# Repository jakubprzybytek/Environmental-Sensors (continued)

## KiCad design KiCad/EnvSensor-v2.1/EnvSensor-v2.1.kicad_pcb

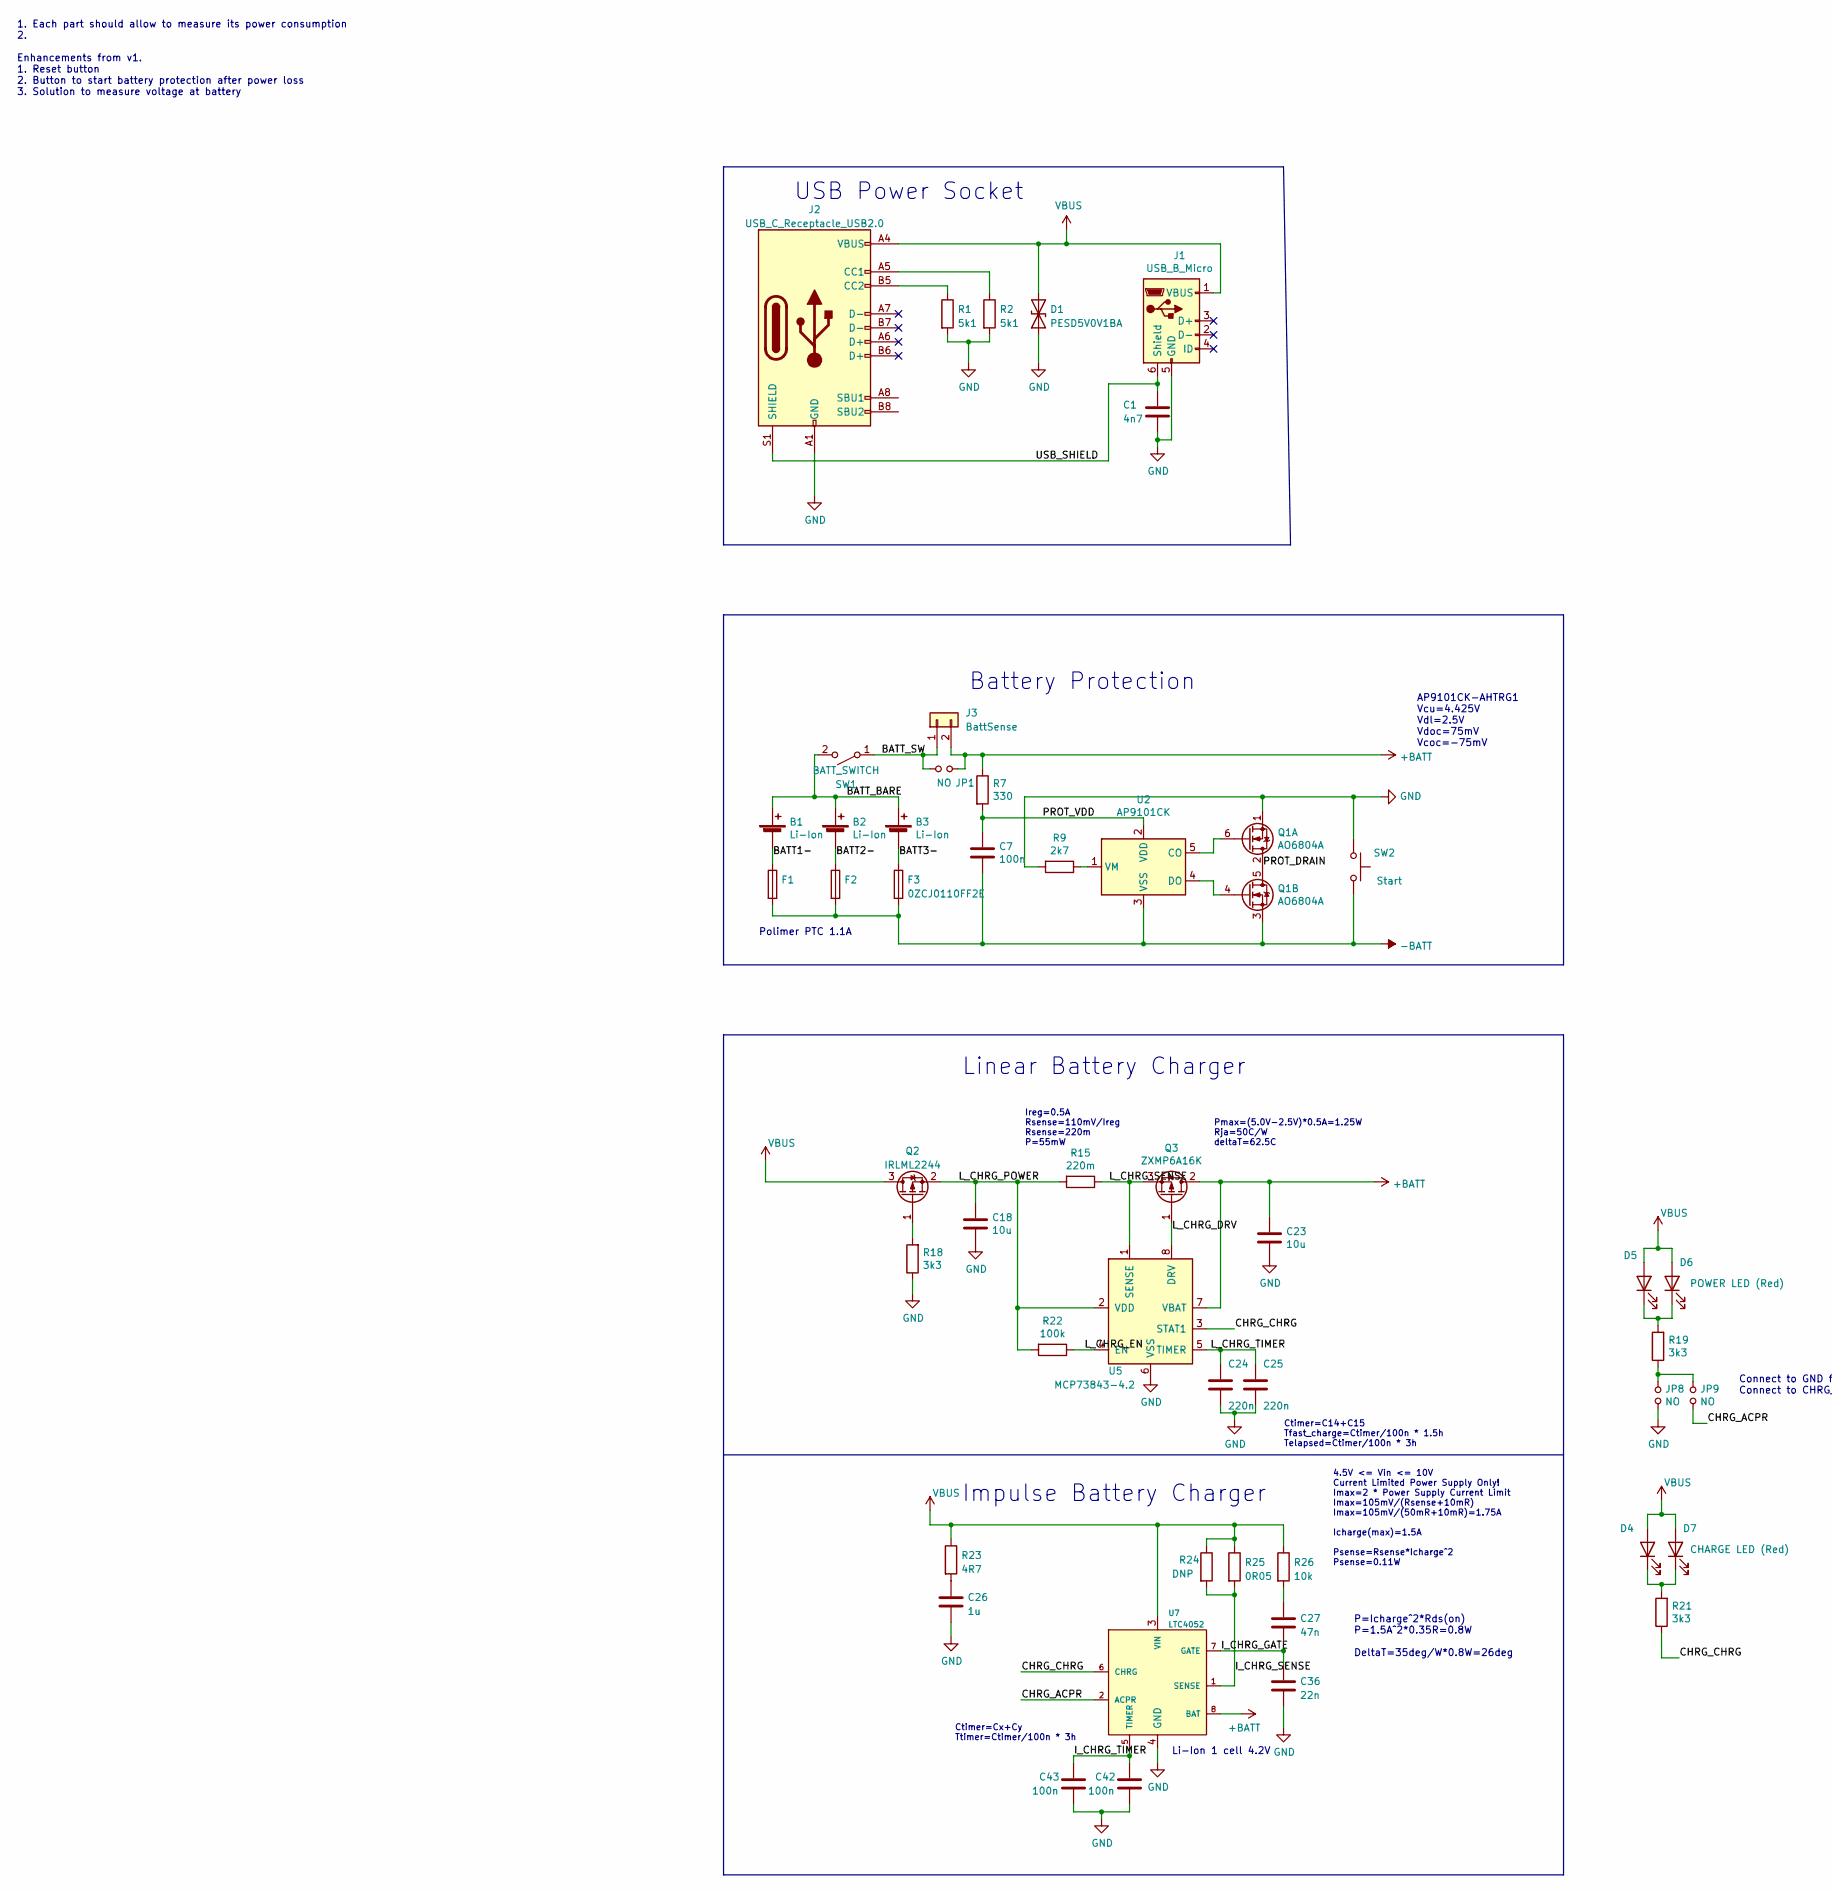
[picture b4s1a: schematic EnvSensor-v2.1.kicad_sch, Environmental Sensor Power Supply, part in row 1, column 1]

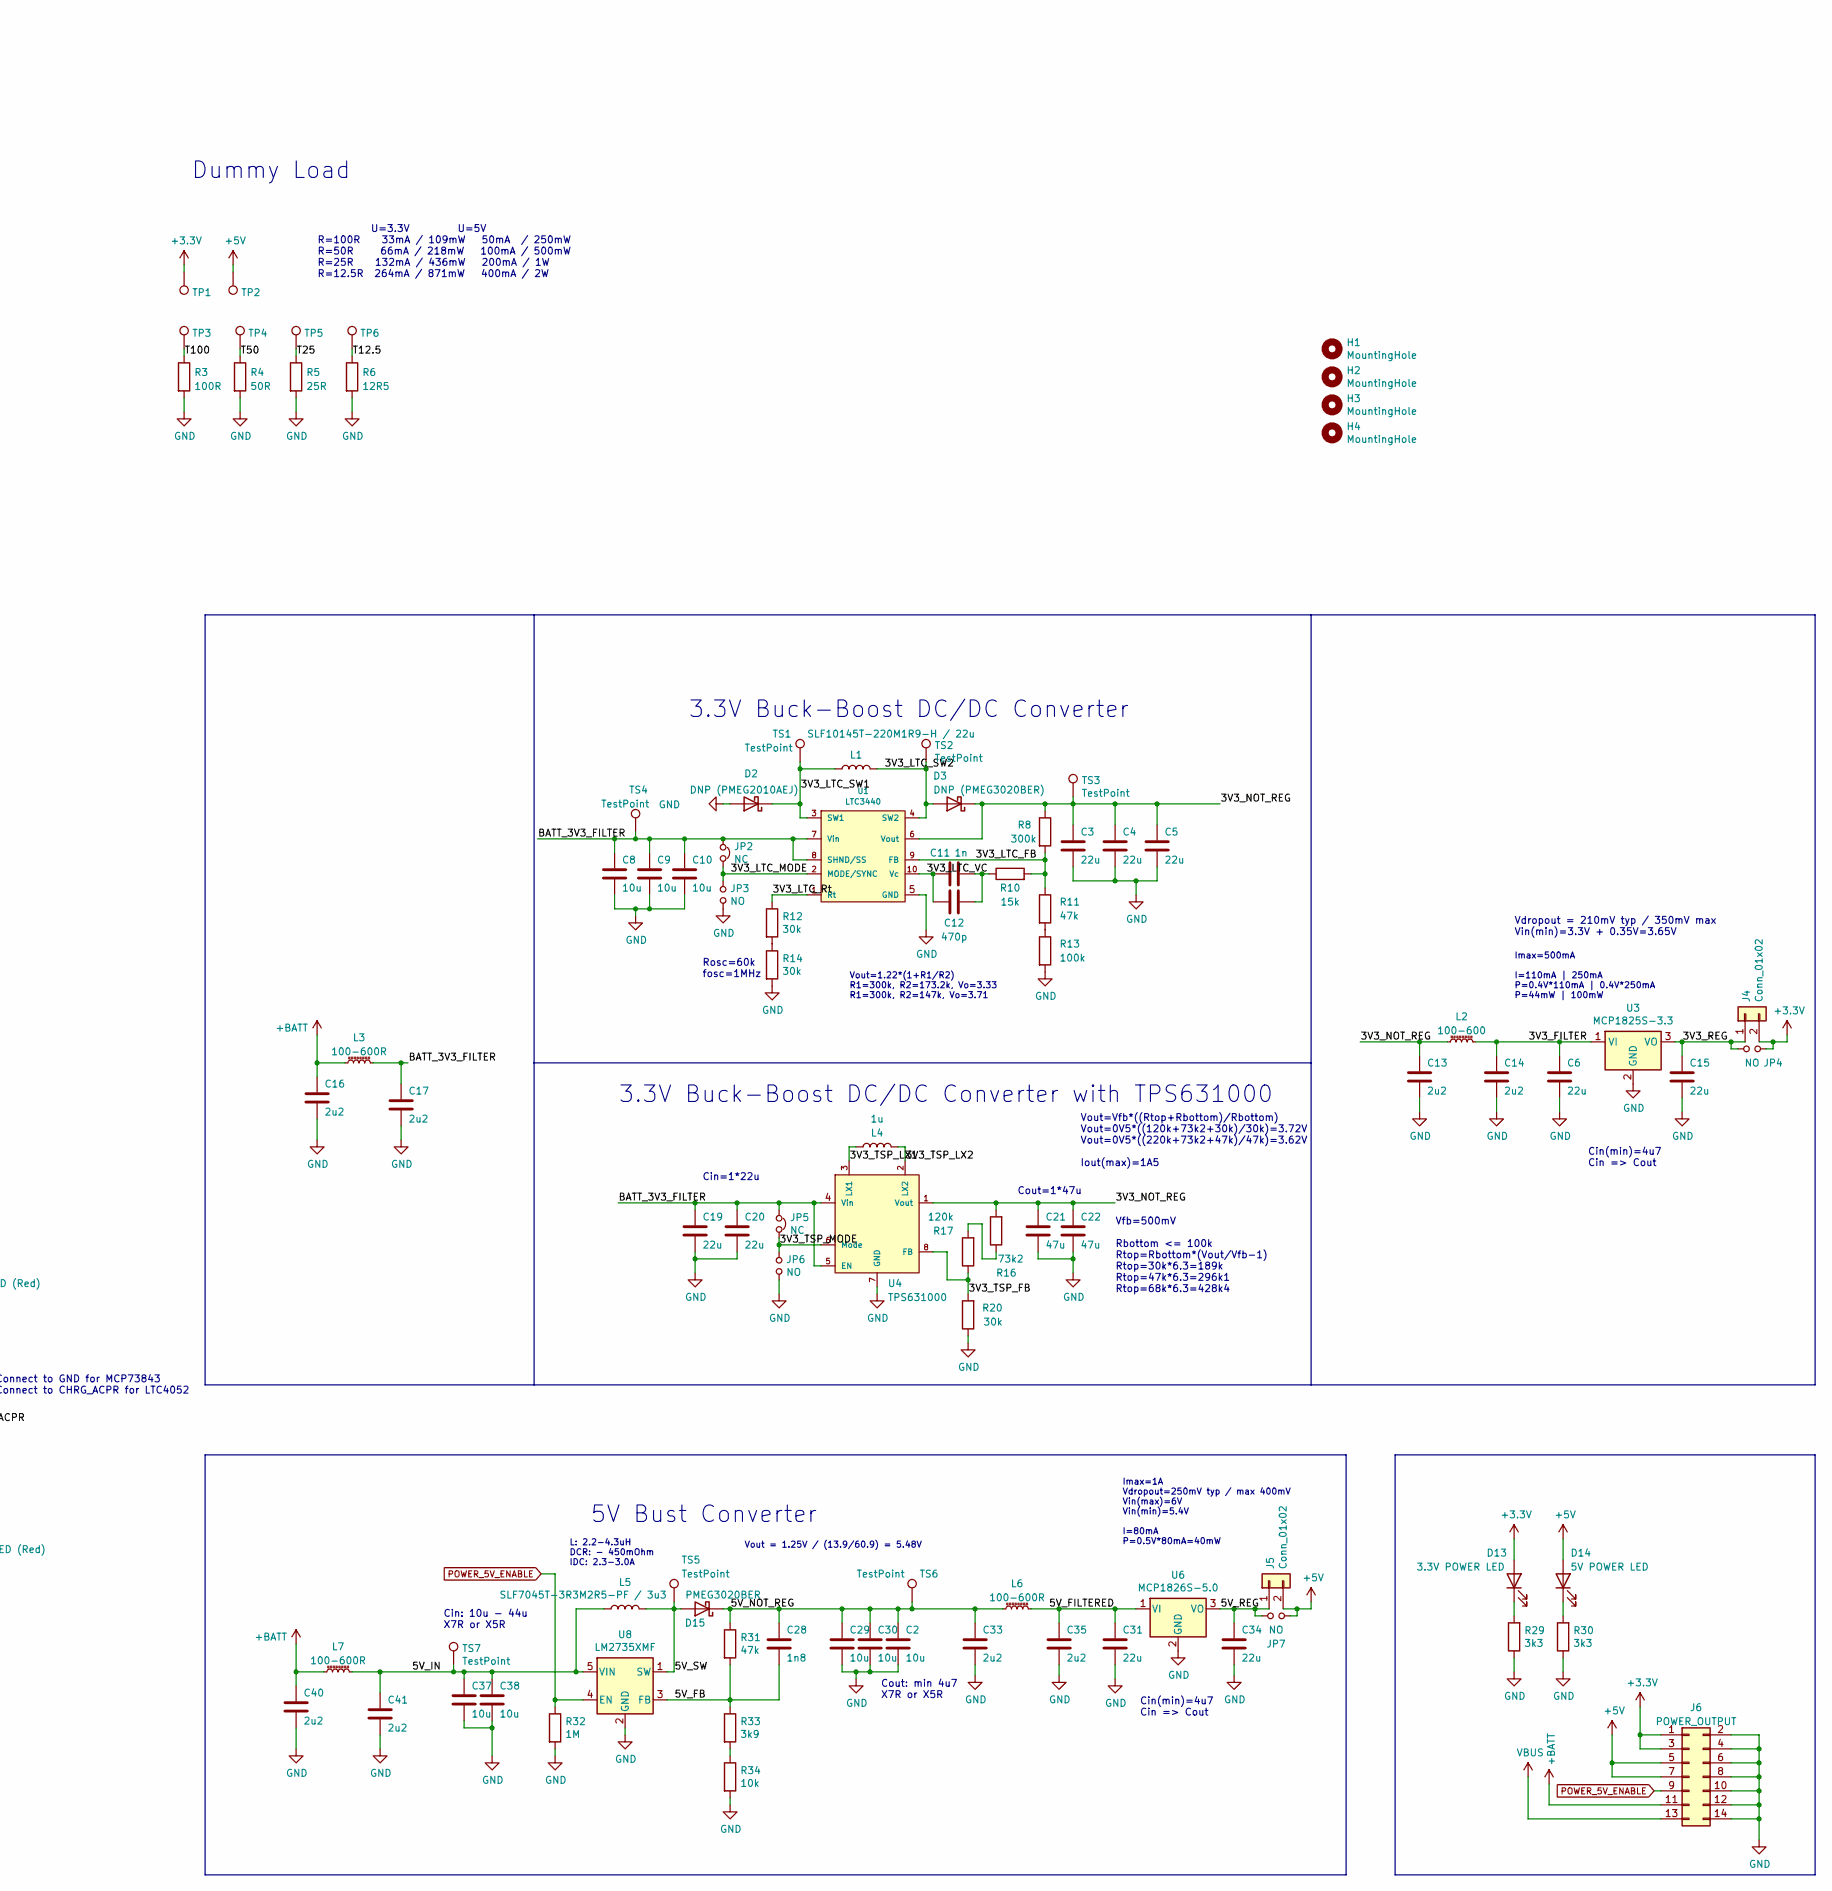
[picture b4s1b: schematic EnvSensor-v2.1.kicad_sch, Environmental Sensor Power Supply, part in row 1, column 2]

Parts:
B1, B2, B3: Li-Ion; BatteryHolder_Keystone_1042_1x18650
C1: 4n7; C_0805_2012Metric
C2, C29, C30: 10u; C_1206_3216Metric
C3, C4, C5, C6, C15, C19, C20, C31, C34: 22u; C_1206_3216Metric
C7, C42, C43: 100n; C_0603_1608Metric
C8, C9, C10, C18, C23, C37, C38: 10u; C_0805_2012Metric
C11: 1n; C_0805_2012Metric
C12: 470p; C_0805_2012Metric
C13, C14, C16, C17, C33, C35, C40, C41: 2u2; C_0805_2012Metric
C21, C22: 47u; C_1206_3216Metric
C24, C25: 220n; C_0805_2012Metric
C26: 1u; C_0805_2012Metric
C27: 47n; C_0805_2012Metric
C28: 1n8; C_0805_2012Metric
C36: 22n; C_0805_2012Metric
D1: PESD5V0V1BA; D_SOD-323
D2: DNP (PMEG2010AEJ); D_SOD-323_HandSoldering
D3: DNP (PMEG3020BER); D_SOD-123
D4, D5: POWER LED; LED_0805_2012Metric
D6: POWER LED (Red); LED_D3.0mm_Horizontal_O3.81mm_Z6.0mm
D7: CHARGE LED (Red); LED_D3.0mm_Horizontal_O3.81mm_Z6.0mm
D13: 3.3V POWER LED; LED_0805_2012Metric
D14: 5V POWER LED; LED_0805_2012Metric
D15: PMEG3020BER; D_SOD-123
F1, F2, F3: 0ZCJ0110FF2E; Fuse_1206_3216Metric
H1, H2, H3, H4: MountingHole; MountingHole_3.2mm_M3
J1: USB_B_Micro; USB_Micro-B_Molex_47346-0001
J2: USB_C_Receptacle_USB2.0; USB_C_Receptacle_HRO_TYPE-C-31-M-12
J3: BattSense; PinHeader_1x02_P2.54mm_Vertical
J4, J5: Conn_01x02; PinHeader_1x02_P2.54mm_Vertical
J6: POWER_OUTPUT; PinHeader_2x07_P2.54mm_Vertical
JP1, JP3, JP4, JP6, JP7, JP8, JP9: NO; SolderJumper-2_P1.3mm_Open_RoundedPad1.0x1.5mm
JP2, JP5: NC; SolderJumper-2_P1.3mm_Bridged_RoundedPad1.0x1.5mm
L1: SLF10145T-220M1R9-H / 22u; L_TDK_SLF10145
L2: 100-600; L_0805_2012Metric
L3, L6, L7: 100-600R; L_0805_2012Metric
L4: 1u; L_TDK_SLF10145
L5: SLF7045T-3R3M2R5-PF / 3u3; L_TDK_SLF7045
Q1: AO6804A; TSOT-23-6
Q2: IRLML2244; SOT-23
Q3: ZXMP6A16K; TO-252-2
R1, R2: 5k1; R_0805_2012Metric
R3: 100R; R_2512_6332Metric
R4: 50R; R_2512_6332Metric
R5: 25R; R_2512_6332Metric
R6: 12R5; R_2512_6332Metric
R7: 330; R_0805_2012Metric
R8: 300k; R_0805_2012Metric
R9: 2k7; R_0805_2012Metric
R10: 15k; R_0805_2012Metric
R11, R31: 47k; R_0805_2012Metric
R12, R14, R20: 30k; R_0805_2012Metric
R13: 100k; R_0805_2012Metric
R15: 220m; R_1206_3216Metric
R16: 73k2; R_0805_2012Metric
R17: 120k; R_0805_2012Metric
R18, R19, R21, R29, R30: 3k3; R_0805_2012Metric
R22: 100k; R_0603_1608Metric
R23: 4R7; R_0805_2012Metric
R24: DNP; R_1206_3216Metric
R25: 0R05; R_1206_3216Metric
R26: 10k; R_0603_1608Metric
R32: 1M; R_0805_2012Metric
R33: 3k9; R_0805_2012Metric
R34: 10k; R_0805_2012Metric
SW1: BATT_SWITCH; SW_Tactile_SPST_Angled_PTS645Vx31-2LFS
SW2: Start; SW_SPST_CK_RS282G05A3
TP1, TP2, TP3, TP4, TP5, TP6: TestPoint; TestPoint_Pad_D1.5mm
TS1, TS2, TS3, TS4, TS5, TS6, TS7: TestPoint; TestPoint_Pad_D1.5mm
U1: LTC3440; MSOP-10_3x3mm_P0.5mm
U2: AP9101CK; SOT-23-5
U3: MCP1825S-3.3; SOT-223-3_TabPin2
U4: TPS631000; SOT-5x3
U5: MCP73843-4.2; MSOP-8_3x3mm_P0.65mm
U6: MCP1826S-5.0; SOT-223-3_TabPin2
U7: LTC4052; MSOP-8_3x3mm_P0.65mm
U8: LM2735XMF; SOT-23-5

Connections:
+3V3: D13.2 (A), J4.2, J6.1, J6.3, JP4.2, TP1.1
+5V: D14.2 (A), J5.2, J6.5, J6.7, JP7.2, TP2.1
+BATT: C16.1, C23.1, C40.1, J3.2, J6.11, JP1.2, L3.1, L7.1, Q3.2 (D), R7.1, U5.7 (VBAT), U7.8 (BAT)
-BATT: C7.2, F1.2, F2.2, F3.2, Q1.3 (S2), SW2.1, U2.3 (VSS)
/3V3_FILTER: C6.1, C14.1, L2.2, U3.1 (VI)
/3V3_LTC_FB: R8.2, R10.2, R11.1, U1.9 (FB)
/3V3_LTC_MODE: JP2.2, JP3.1, U1.2 (MODE/SYNC)
/3V3_LTC_Rt: R12.1, U1.1 (Rt)
/3V3_LTC_SW1: D2.1 (K), L1.1, TS1.1, U1.3 (SW1)
/3V3_LTC_SW2: D3.2 (A), L1.2, TS2.1, U1.4 (SW2)
/3V3_LTC_VC: C11.2, C12.2, U1.10 (Vc)
/3V3_NOT_REG: C3.1, C4.1, C5.1, C13.1, C21.1, C22.1, D3.1 (K), L2.1, R8.1, R16.2, TS3.1, U1.6 (Vout), U4.1 (Vout)
/3V3_REG: C15.1, J4.1, JP4.1, U3.3 (VO)
/3V3_TSP_FB: R17.1, R20.2, U4.8 (FB)
/3V3_TSP_LX1: L4.1, U4.3 (LX1)
/3V3_TSP_LX2: L4.2, U4.2 (LX2)
/3V3_TSP_MODE: JP5.2, JP6.1, U4.6 (Mode)
/5V_FB: C28.2, R31.2, R33.1, U8.3 (FB)
/5V_FILTERED: C31.1, C35.1, L6.2, U6.1 (VI)
/5V_IN: C37.1, C38.1, C41.1, L5.1, L7.2, TS7.1, U8.5 (VIN)
/5V_NOT_REG: C2.1, C28.1, C29.1, C30.1, C33.1, D15.1 (K), L6.1, R31.1, TS6.1
/5V_REG: C34.1, J5.1, JP7.1, U6.3 (VO)
/5V_SW: D15.2 (A), L5.2, TS5.1, U8.1 (SW)
/BATT1-: B1.2 (-), F1.1
/BATT2-: B2.2 (-), F2.1
/BATT3-: B3.2 (-), F3.1
/BATT_3V3_FILTER: C8.1, C9.1, C10.1, C17.1, C19.1, C20.1, JP2.1, JP5.1, L3.2, TS4.1, U1.7 (Vin), U1.8 (SHND/SS), U4.4 (Vin), U4.5 (EN)
/BATT_BARE: B1.1 (+), B2.1 (+), B3.1 (+), SW1.2 (B)
/BATT_SW: J3.1, JP1.1, SW1.1 (A)
/CHRG_ACPR: JP9.2, U7.2 (ACPR)
/CHRG_CHRG: R21.1, U5.3 (STAT1), U7.6 (CHRG)
/I_CHRG_GATE: C27.2, C36.1, U7.7 (GATE)
/I_CHRG_SENSE: R24.2, R25.2, U7.1 (SENSE)
/I_CHRG_TIMER: C42.1, C43.1, U7.5 (TIMER)
/L_CHRG_DRV: Q3.1 (G), U5.8 (DRV)
/L_CHRG_EN: R22.1, U5.4 (EN)
/L_CHRG_POWER: C18.1, Q2.2 (S), R15.2, R22.2, U5.2 (VDD)
/L_CHRG_SENSE: Q3.3 (S), R15.1, U5.1 (SENSE)
/L_CHRG_TIMER: C24.1, C25.1, U5.5 (TIMER)
/PROT_DRAIN: Q1.2 (D2), Q1.5 (D2)
/PROT_VDD: C7.1, R7.2, U2.2 (VDD)
/T12.5: R6.1, TP6.1
/T25: R5.1, TP5.1
/T50: R4.1, TP4.1
/T100: R3.1, TP3.1
/USB_SHIELD: C1.1, J1.6 (Shield), J2.S1 (SHIELD)
GND: C1.2, C2.2, C3.2, C4.2, C5.2, C6.2, C8.2, C9.2, C10.2, C13.2, C14.2, C15.2, C16.2, C17.2, C18.2, C19.2, C20.2, C21.2, C22.2, C23.2, C24.2, C25.2, C26.2, C29.2, C30.2, C31.2, C33.2, C34.2, C35.2, C36.2, C37.2, C38.2, C40.2, C41.2, C42.2, C43.2, D1.1 (A1), D2.2 (A), J1.5 (GND), J2.A1 (GND), J2.A12 (GND), J2.B1 (GND), J2.B12 (GND), J6.2, J6.4, J6.6, J6.8, J6.10, J6.12, J6.14, JP3.2, JP6.2, JP8.2, Q1.1 (S2), R1.2, R2.2, R3.2, R4.2, R5.2, R6.2, R9.2, R13.2, R14.2, R18.1, R20.1, R29.1, R30.1, R32.2, R34.2, SW2.2, U1.5 (GND), U3.2 (GND), U4.7 (GND), U5.6 (VSS), U6.2 (GND), U7.4 (GND), U8.2 (GND)
unnamed: C11.1, C12.1, R10.1
unnamed: C26.1, R23.2
unnamed: C27.1, R26.2
unnamed: D4.1 (K), D7.1 (K), R21.2
unnamed: D5.1 (K), D6.1 (K), R19.2
unnamed: D13.1 (K), R29.2
unnamed: D14.1 (K), R30.2
unnamed: J2.A5 (CC1), R2.1
unnamed: J2.B5 (CC2), R1.1
unnamed: JP8.1, JP9.1, R19.1
unnamed: Q1.4 (G2), U2.4 (DO)
unnamed: Q1.6 (G2), U2.5 (CO)
unnamed: Q2.1 (G), R18.2
unnamed: R9.1, U2.1 (VM)
unnamed: R11.2, R13.1
unnamed: R12.2, R14.1
unnamed: R16.1, R17.2
unnamed: R33.2, R34.1
POWER_5V_ENABLE: J6.9, R32.1, U8.4 (EN)
VBUS: D1.2 (A2), D4.2 (A), D5.2 (A), D6.2 (A), D7.2 (A), J1.1 (VBUS), J2.A4 (VBUS), J2.A9 (VBUS), J2.B4 (VBUS), J2.B9 (VBUS), J6.13, Q2.3 (D), R23.1, R24.1, R25.1, R26.1, U7.3 (VIN)

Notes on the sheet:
L: 2.2-4.3uH DCR: - 450mOhm IDC: 2.3-3.0A
AP9101CK-AHTRG1 Vcu=4.425V Vdl=2.5V Vdoc=75mV Vcoc=-75mV
Cout: min 4u7 X7R or X5R
1. Each part should allow to measure its power consumption 2. Enhancements from v1. 1. Reset button 2. Button to start battery protection after power loss 3. Solution to measure voltage at battery
Linear Battery Charger
Connect to GND for MCP73843 Connect to CHRG_ACPR for LTC4052
5V Bust Converter
Ireg=0.5A Rsense=110mV/Ireg Rsense=220m P=55mW
Cin: 10u - 44u X7R or X5R
Pmax=(5.0V-2.5V)*0.5A=1.25W Rja=50C/W deltaT=62.5C
Ctimer=Cx+Cy Ttimer=Ctimer/100n * 3h
Vfb=500mV Rbottom <= 100k Rtop=Rbottom*(Vout/Vfb-1) Rtop=30k*6.3=189k Rtop=47k*6.3=296k1 Rtop=68k*6.3=428k4
Li-Ion 1 cell 4.2V
3.3V Buck-Boost DC/DC Converter
Impulse Battery Charger
Cin(min)=4u7 Cin => Cout
Imax=500mA I=110mA | 250mA P=0.4V*110mA | 0.4V*250mA P=44mW | 100mW
Cout=1*47u
USB Power Socket
4.5V <= Vin <= 10V Current Limited Power Supply Only! Imax=2 * Power Supply Current Limit Imax=105mV/(Rsense+10mR) Imax=105mV/(50mR+10mR)=1.75A Icharge(max)=1.5A Psense=Rsense*Icharge^2 Psense=0.11W
Rosc=60k fosc=1MHz
Cin=1*22u
Ctimer=C14+C15 Tfast_charge=Ctimer/100n * 1.5h Telapsed=Ctimer/100n * 3h
Dummy Load
3.3V Buck-Boost DC/DC Converter with TPS631000
Vdropout = 210mV typ / 350mV max Vin(min)=3.3V + 0.35V=3.65V
Vout=1.22*(1+R1/R2) R1=300k, R2=173.2k, Vo=3.33 R1=300k, R2=147k, Vo=3.71
P=Icharge^2*Rds(on) P=1.5A^2*0.35R=0.8W DeltaT=35deg/W*0.8W=26deg
U=3.3V U=5V R=100R 33mA / 109mW 50mA / 250mW R=50R 66mA / 218mW 100mA / 500mW R=25R 132mA / 436mW 200mA / 1W R=12.5R 264mA / 871mW 400mA / 2W
Imax=1A Vdropout=250mV typ / max 400mV Vin(max)=6V Vin(min)=5.4V I=80mA P=0.5V*80mA=40mW
Vout=Vfb*((Rtop+Rbottom)/Rbottom) Vout=0V5*((120k+73k2+30k)/30k)=3.72V Vout=0V5*((220k+73k2+47k)/47k)=3.62V Iout(max)=1A5
Polimer PTC 1.1A
Vout = 1.25V / (13.9/60.9) = 5.48V
Battery Protection

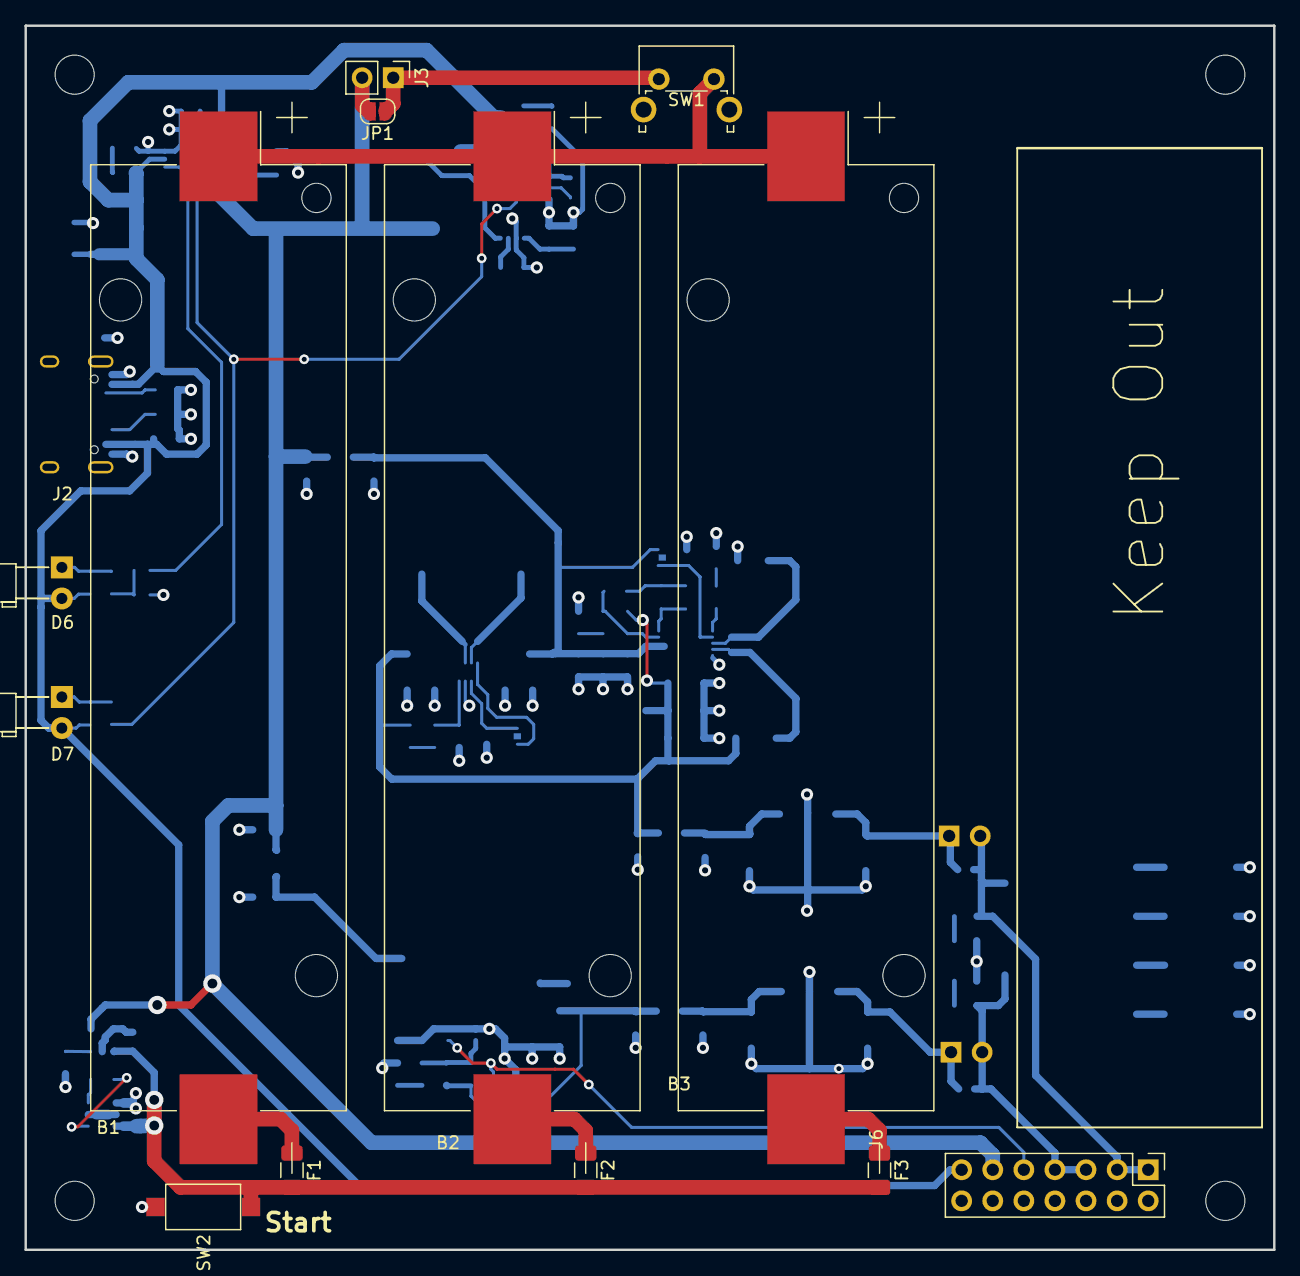
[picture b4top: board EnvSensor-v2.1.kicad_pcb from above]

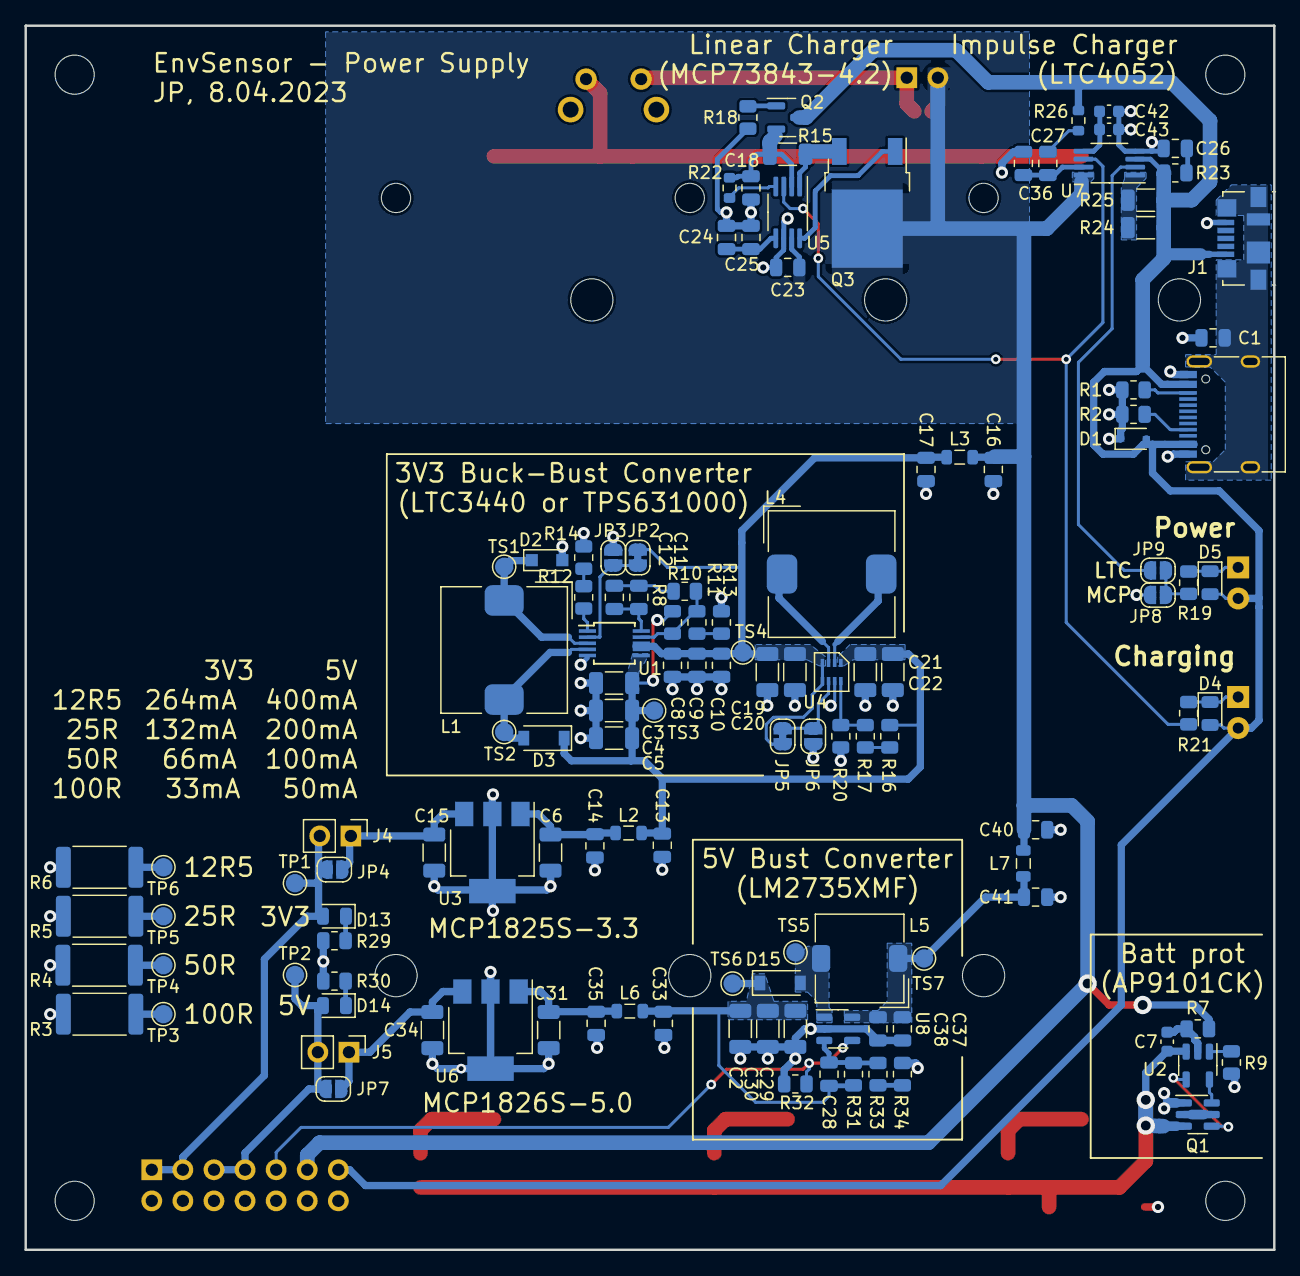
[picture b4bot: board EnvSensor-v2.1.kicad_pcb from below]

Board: 4 copper layers, 102.0 x 100.0 mm, 141 parts (124 on the bottom side), 67 nets.

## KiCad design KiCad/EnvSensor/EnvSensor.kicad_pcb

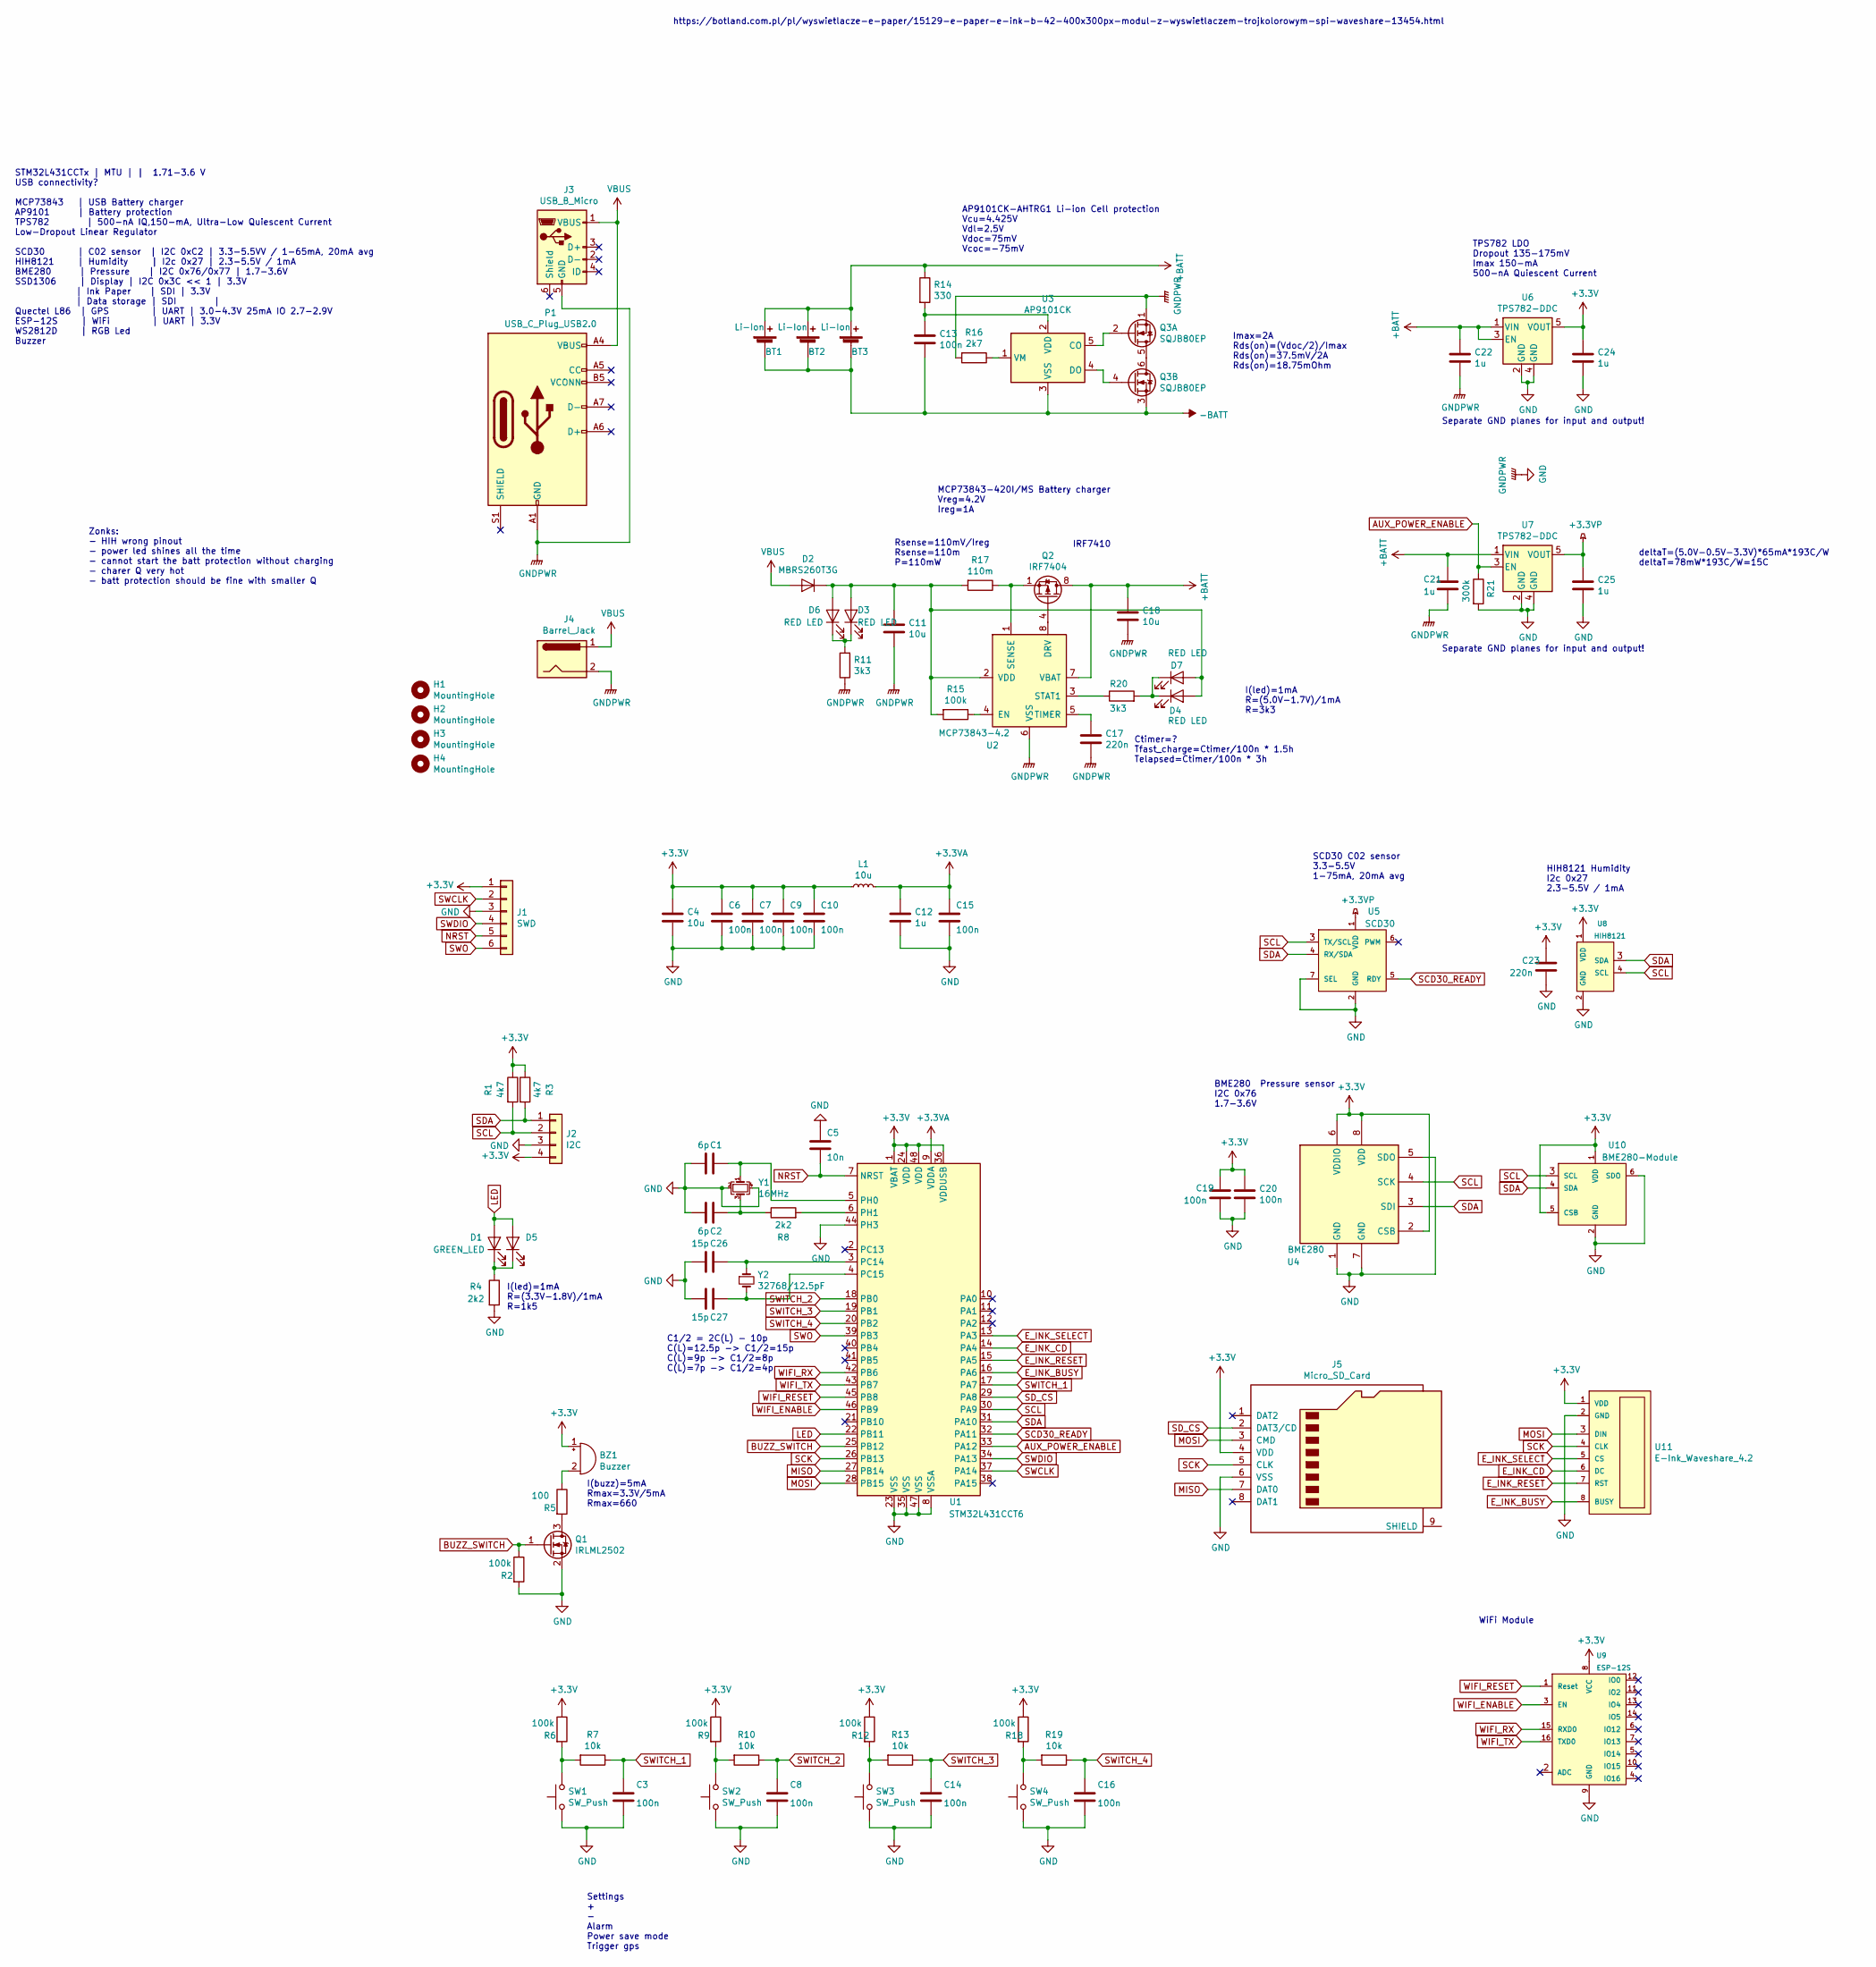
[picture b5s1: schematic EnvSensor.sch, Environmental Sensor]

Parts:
BT1, BT2, BT3: Li-Ion; BatteryHolder_Keystone_1042_1x18650
BZ1: Buzzer; Laudity_SPB45
C1, C2: 6p; C_0805_2012Metric
C3, C6, C7, C8, C9, C10, C13, C14, C15, C16, C19, C20: 100n; C_0603_1608Metric
C4, C11, C18: 10u; C_0805_2012Metric
C5: 10n; C_0805_2012Metric
C12, C21, C22, C24, C25: 1u; C_0805_2012Metric
C17, C23: 220n; C_0805_2012Metric
C26, C27: 15p; C_0805_2012Metric
D1: GREEN_LED; LED_0805_2012Metric
D2: MBRS260T3G; D_SMB
D3, D4: RED LED; LED_0805_2012Metric
D5: GREEN_LED; LED_D3.0mm
D6, D7: RED LED; LED_D3.0mm_Horizontal_O3.81mm_Z10.0mm
H1, H2, H3, H4: MountingHole; MountingHole_3.2mm_M3
J1: SWD; PinHeader_1x06_P2.54mm_Horizontal
J2: I2C; PinSocket_1x04_P2.54mm_Vertical
J3: USB_B_Micro; USB_Micro-B_Molex_47346-0001
J4: Barrel_Jack; PowerSocketSMD
J5: Micro_SD_Card; microSD_HC_Hirose_DM3AT-SF-PEJM5
L1: 10u; L_0805_2012Metric
P1: USB_C_Plug_USB2.0; USB_C_Receptacle_Adam_Tech
Q1: IRLML2502; SOT-23
Q2: IRF7404; SOIC-8_3.9x4.9mm_P1.27mm
Q3: SQJB80EP; PowerPAK_SO-8_Dual
R1, R3: 4k7; R_0805_2012Metric
R2, R6, R9, R12, R15, R18: 100k; R_0603_1608Metric
R4, R8: 2k2; R_0805_2012Metric
R5: 100; R_0805_2012Metric
R7, R10, R13, R19: 10k; R_0603_1608Metric
R11, R20: 3k3; R_0805_2012Metric
R14: 330; R_0805_2012Metric
R16: 2k7; R_0805_2012Metric
R17: 110m; R_2512_6332Metric
R21: 300k; R_0805_2012Metric
SW1, SW2, SW3, SW4: SW_Push; SW_SPST_PTS645
U1: STM32L431CCT6; LQFP-48_7x7mm_P0.5mm
U2: MCP73843-4.2; MSOP-8_3x3mm_P0.65mm
U3: AP9101CK; SOT-23-5
U4: BME280; Bosch_LGA-8_2.5x2.5mm_P0.65mm_ClockwisePinNumbering
U5: SCD30
U6, U7: TPS782-DDC; SOT-23-5
U8: HIH8121; PinHeader_1x04_P1.27mm_Vertical
U9: ESP-12S
U10: BME280-Module
U11: E-Ink_Waveshare_4.2; 4.2inch_E-Ink
Y1: 16MHz; Crystal_SMD_Abracon_ABM3B-4Pin_5.0x3.2mm
Y2: 32768/12.5pF; Crystal_SMD_MicroCrystal_CC7V-T1A-2Pin_3.2x1.5mm

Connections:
+3.3VA: C12.1, C15.1, L1.2, U1.9 (VDDA)
+3.3VP: C25.1, U5.1 (VDD), U7.5 (VOUT)
+3V3: BZ1.1 (-), C4.1, C6.1, C7.1, C9.1, C10.1, C19.1, C20.1, C23.1, C24.1, J1.1, J2.4, J5.4 (VDD), L1.1, R1.1, R3.1, R6.1, R9.1, R12.1, R18.1, U1.1 (VBAT), U1.24 (VDD), U1.36 (VDDUSB), U1.48 (VDD), U4.2 (CSB), U4.6 (VDDIO), U4.8 (VDD), U6.5 (VOUT), U8.1 (VDD), U9.8 (VCC), U10.1 (VDD), U10.5 (CSB), U11.1 (VDD)
+BATT: BT1.1 (+), BT2.1 (+), BT3.1 (+), C18.1, C21.1, C22.1, Q2.5 (D), Q2.6 (D), Q2.7 (D), Q2.8 (D), R14.1, U2.7 (VBAT), U6.1 (VIN), U6.3 (EN), U7.1 (VIN)
-BATT: BT1.2 (-), BT2.2 (-), BT3.2 (-), C13.2, Q3.3 (S2), U3.3 (VSS)
AUX_POWER_ENABLE: R21.1, U1.33 (PA12), U7.3 (EN)
BUZZ_SWITCH: Q1.1 (G), R2.1, U1.25 (PB12)
E_INK_BUSY: U1.16 (PA6), U11.8 (BUSY)
E_INK_CD: U1.14 (PA4), U11.6 (DC)
E_INK_RESET: U1.15 (PA5), U11.7 (RST)
E_INK_SELECT: U1.13 (PA3), U11.5 (CS)
GND: C1.2, C2.2, C3.2, C4.2, C5.1, C6.2, C7.2, C8.2, C9.2, C10.2, C11.2, C12.2, C14.2, C15.2, C16.2, C17.2, C18.2, C19.2, C20.2, C21.2, C22.2, C23.2, C24.2, C25.2, C26.2, C27.2, J1.3, J2.3, J3.5 (GND), J4.2, J5.6 (VSS), P1.A1 (GND), P1.A12 (GND), P1.B1 (GND), P1.B12 (GND), Q1.2 (S), Q3.1 (S2), R2.2, R4.2, R11.1, R16.2, R21.2, SW1.1, SW2.1, SW3.1, SW4.1, U1.8 (VSSA), U1.23 (VSS), U1.35 (VSS), U1.44 (PH3), U1.47 (VSS), U2.6 (VSS), U4.1 (GND), U4.5 (SDO), U4.7 (GND), U5.2 (GND), U5.7 (SEL), U6.2 (GND), U6.4 (GND), U7.2 (GND), U7.4 (GND), U8.2 (GND), U9.9 (GND), U10.2 (GND), U10.6 (SDO), U11.2 (GND), Y1.2, Y1.4
LED: D1.2 (A), D5.2 (A), U1.22 (PB11)
MISO: J5.7 (DAT0), U1.27 (PB14)
MOSI: J5.3 (CMD), U1.28 (PB15), U11.3 (DIN)
NRST: C5.2, J1.5, U1.7 (NRST)
unnamed: BZ1.2 (+), R5.1
unnamed: C1.1, U1.5 (PH0), Y1.1
unnamed: C2.1, R8.1, Y1.3
unnamed: C11.1, D2.1 (K), D3.2 (A), D4.2 (A), D6.2 (A), D7.2 (A), R15.2, R17.2, U2.2 (VDD)
unnamed: C13.1, R14.2, U3.2 (VDD)
unnamed: C17.1, U2.5 (TIMER)
unnamed: C26.1, U1.3 (PC14), Y2.1
unnamed: C27.1, U1.4 (PC15), Y2.2
unnamed: D1.1 (K), D5.1 (K), R4.1
unnamed: D3.1 (K), D6.1 (K), R11.2
unnamed: D4.1 (K), D7.1 (K), R20.2
unnamed: Q1.3 (D), R5.2
unnamed: Q2.1 (S), Q2.2 (S), Q2.3 (S), R17.1, U2.1 (SENSE)
unnamed: Q2.4 (G), U2.8 (DRV)
unnamed: Q3.2 (G2), U3.5 (CO)
unnamed: Q3.4 (G2), U3.4 (DO)
unnamed: Q3.5 (D2), Q3.6 (D2)
unnamed: R6.2, R7.2, SW1.2
unnamed: R8.2, U1.6 (PH1)
unnamed: R9.2, R10.2, SW2.2
unnamed: R12.2, R13.2, SW3.2
unnamed: R15.1, U2.4 (EN)
unnamed: R16.1, U3.1 (VM)
unnamed: R18.2, R19.2, SW4.2
unnamed: R20.1, U2.3 (STAT1)
SCD30_READY: U1.32 (PA11), U5.5 (RDY)
SCK: J5.5 (CLK), U1.26 (PB13), U11.4 (CLK)
SCL: J2.2, R1.2, U1.30 (PA9), U4.4 (SCK), U5.3 (TX/SCL), U8.4 (SCL), U10.3 (SCL)
SDA: J2.1, R3.2, U1.31 (PA10), U4.3 (SDI), U5.4 (RX/SDA), U8.3 (SDA), U10.4 (SDA)
SD_CS: J5.2 (DAT3/CD), U1.29 (PA8)
SWCLK: J1.2, U1.37 (PA14)
SWDIO: J1.4, U1.34 (PA13)
SWITCH_1: C3.1, R7.1, U1.17 (PA7)
SWITCH_2: C8.1, R10.1, U1.18 (PB0)
SWITCH_3: C14.1, R13.1, U1.19 (PB1)
SWITCH_4: C16.1, R19.1, U1.20 (PB2)
SWO: J1.6, U1.39 (PB3)
VBUS: D2.2 (A), J3.1 (VBUS), J4.1, P1.A4 (VBUS), P1.A9 (VBUS), P1.B4 (VBUS), P1.B9 (VBUS)
WIFI_ENABLE: U1.46 (PB9), U9.3 (EN)
WIFI_RESET: U1.45 (PB8), U9.1 (Reset)
WIFI_RX: U1.42 (PB6), U9.15 (RXD0)
WIFI_TX: U1.43 (PB7), U9.16 (TXD0)

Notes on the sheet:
STM32L431CCTx | MTU | | 1.71-3.6 V USB connectivity? MCP73843 | USB Battery charger AP9101 | Battery protection TPS782 | 500-nA IQ,150-mA, Ultra-Low Quiescent Current Low-Dropout Linear Regulator SCD30 | C02 sensor | I2C 0xC2 | 3.3-5.5VV / 1-65mA, 20mA avg HIH8121 | Humidity | I2c 0x27 | 2.3-5.5V /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
https://botland.com.pl/pl/wyswietlacze-e-paper/15129-e-paper-e-ink-b-42-400x300px-modul-z-wyswietlaczem-trojkolorowym-spi-waveshare-13454.html
TPS782 LDO Dropout 135-175mV Imax 150-mA 500-nA Quiescent Current
Separate GND planes for input and output!
MCP73843-420I/MS Battery charger Vreg=4.2V Ireg=1A
I(led)=1mA R=(5.0V-1.7V)/1mA R=3k3
Ctimer=? Tfast_charge=Ctimer/100n * 1.5h Telapsed=Ctimer/100n * 3h
Rsense=110mV/Ireg Rsense=110m P=110mW
IRF7410
AP9101CK-AHTRG1 Li-ion Cell protection Vcu=4.425V Vdl=2.5V Vdoc=75mV Vcoc=-75mV
SCD30 C02 sensor 3.3-5.5V 1-75mA, 20mA avg
HIH8121 Humidity I2c 0x27 2.3-5.5V / 1mA
Zonks: - HIH wrong pinout - power led shines all the time - cannot start the batt protection without charging - charer Q very hot - batt protection should be fine with smaller Q
BME280 Pressure sensor I2C 0x76 1.7-3.6V
I(led)=1mA R=(3.3V-1.8V)/1mA R=1k5
WiFi Module
Settings + - Alarm Power save mode Trigger gps
Imax=2A Rds(on)=(Vdoc/2)/Imax Rds(on)=37.5mV/2A Rds(on)=18.75mOhm
C1/2 = 2C(L) - 10p C(L)=12.5p -> C1/2=15p C(L)=9p -> C1/2=8p C(L)=7p -> C1/2=4p
I(buzz)=5mA Rmax=3.3V/5mA Rmax=660
deltaT=(5.0V-0.5V-3.3V)*65mA*193C/W deltaT=78mW*193C/W=15C
